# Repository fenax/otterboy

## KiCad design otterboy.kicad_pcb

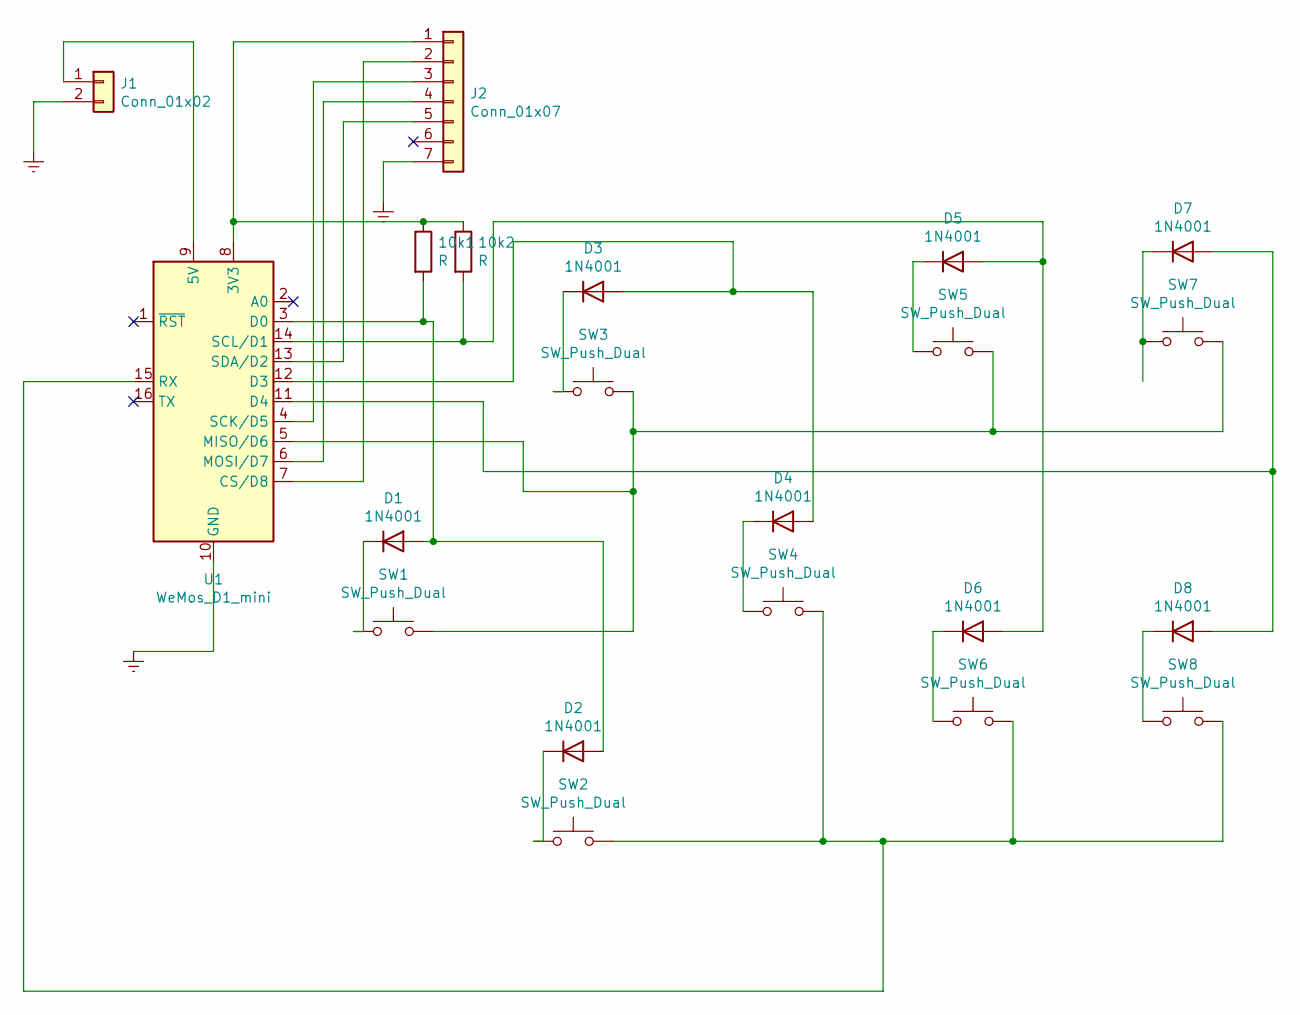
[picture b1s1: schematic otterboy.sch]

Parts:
10k1, 10k2: R; R_Axial_DIN0204_L3.6mm_D1.6mm_P5.08mm_Horizontal
D1, D2, D3, D4, D5, D6, D7, D8: 1N4001; D_T-1_P5.08mm_Horizontal
J1: Conn_01x02; PinHeader_1x02_P2.54mm_Vertical
J2: Conn_01x07; PinHeader_1x07_P2.54mm_Vertical
SW1, SW2, SW3, SW4, SW5, SW6, SW7, SW8: SW_Push_Dual; SW_PUSH_6mm_H5mm
U1: WeMos_D1_mini; WEMOS_D1_mini_light

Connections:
Earth: J1.2, J2.7, U1.10 (GND)
unnamed: 10k1.1, 10k2.1, J2.1, U1.8 (3V3)
unnamed: 10k1.2, D1.2 (A), D2.2 (A), U1.3 (D0)
unnamed: 10k2.2, D5.2 (A), D6.2 (A), U1.14 (SCL/D1)
unnamed: D1.1 (K), SW1.1
unnamed: D2.1 (K), SW2.1
unnamed: D3.1 (K), SW3.1
unnamed: D3.2 (A), D4.2 (A), U1.12 (D3)
unnamed: D4.1 (K), SW4.1
unnamed: D5.1 (K), SW5.1
unnamed: D6.1 (K), SW6.1
unnamed: D7.1 (K), SW7.1
unnamed: D7.2 (A), D8.2 (A), U1.11 (D4)
unnamed: D8.1 (K), SW8.1
unnamed: J1.1, U1.9 (5V)
unnamed: J2.2, U1.7 (CS/D8)
unnamed: J2.3, U1.4 (SCK/D5)
unnamed: J2.4, U1.6 (MOSI/D7)
unnamed: J2.5, U1.13 (SDA/D2)
unnamed: SW1.2, SW3.2, SW5.2, SW7.2, U1.5 (MISO/D6)
unnamed: SW2.2, SW4.2, SW6.2, SW8.2, U1.15 (RX)

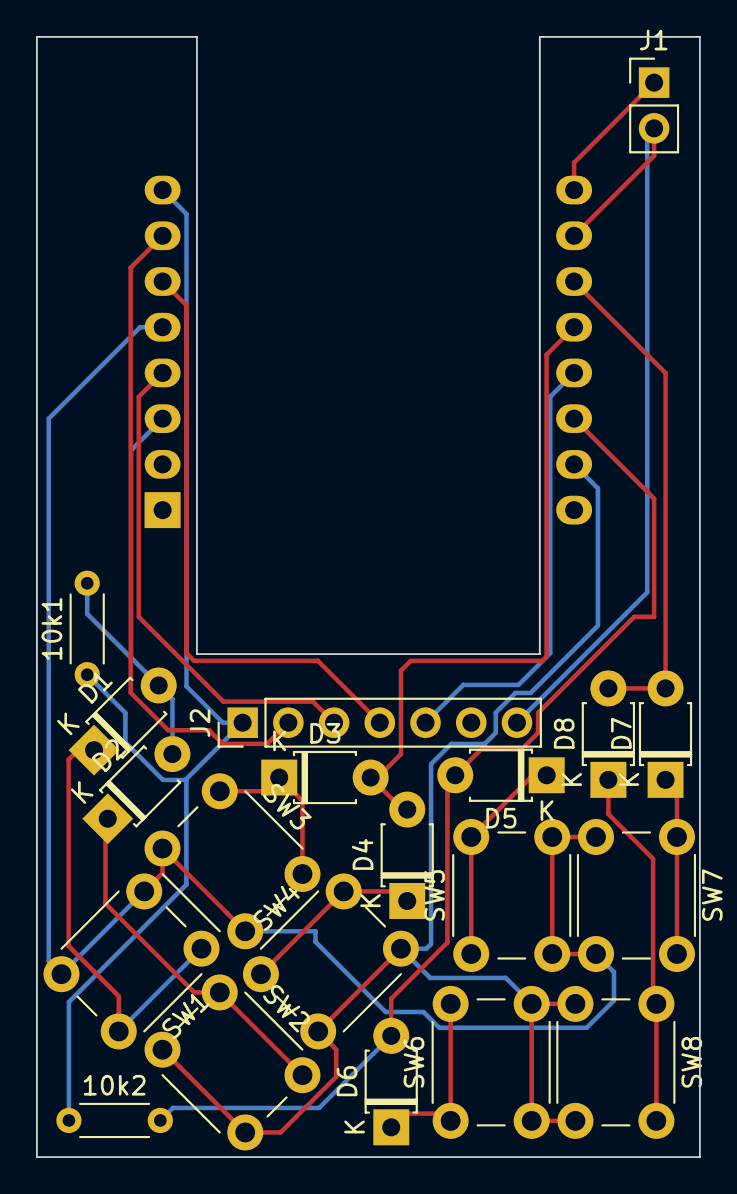
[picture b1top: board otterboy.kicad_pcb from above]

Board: 2 copper layers, 36.8 x 62.2 mm, 21 parts (1 on the bottom side), 21 nets.
